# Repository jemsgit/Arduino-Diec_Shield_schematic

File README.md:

Arduino-Diec_Shield_schematic
=======

Schematics and boards

Arduino Diecimila - shc and brd for Arduino Atmega 168p
Arduino Shield - shield for servo, sound, led and power supply

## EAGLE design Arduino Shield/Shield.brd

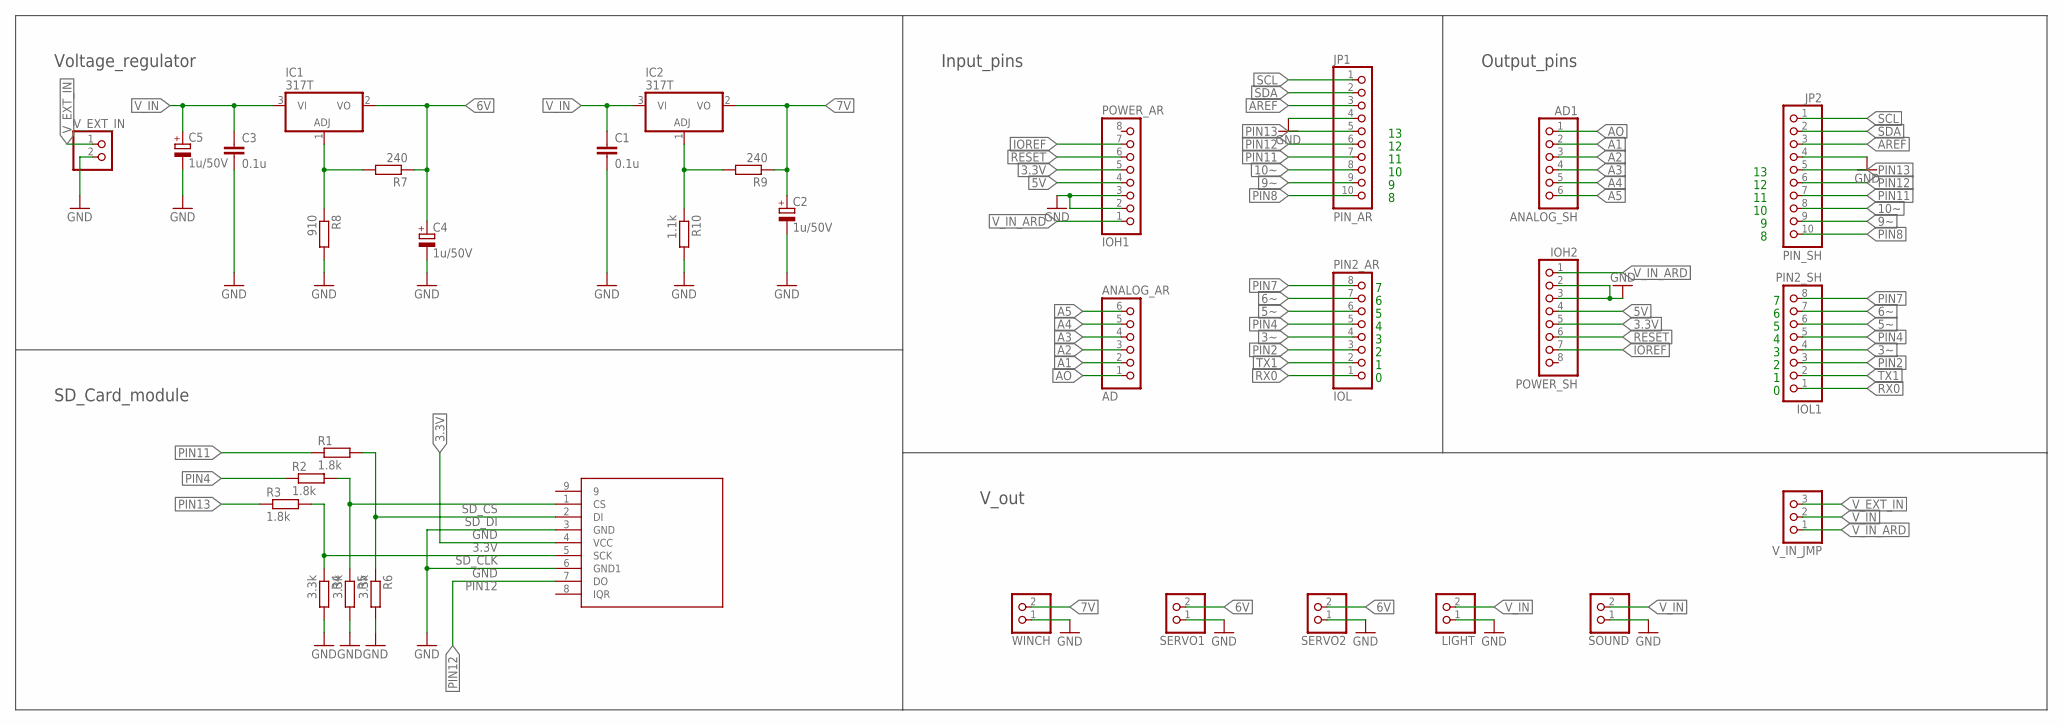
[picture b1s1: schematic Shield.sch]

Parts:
AD: ANALOG_AR; 1X06@1
AD1: ANALOG_SH; 1X06@1
C1, C3: 0.1u; C0805
C2, C4, C5: 1u/50V; E3,5-8
IC1, IC2: 317T; TO220H
IOH1: POWER_AR; 1X08
IOH2: POWER_SH; 1X08
IOL: PIN2_AR; 1X08@1
IOL1: PIN2_SH; 1X08@1
JP1: PIN_AR; 1X10
JP2: PIN_SH; 1X10
LIGHT: PINHD-1X2; 1X02
R1, R2, R3: 1.8k; R0805
R4, R5, R6: 3.3k; R0805
R7, R9: 240; R0805
R8: 910; R0805
R10: 1.1k; R0805
SERVO1, SERVO2: PINHD-1X2; 1X02
SOUND: PINHD-1X2; 1X02
U$1: SDCARDVAR2; SDCMF-10915W010
V_EXT_IN: PINHD-1X2; 1X02
V_IN_JMP: PINHD-1X3; 1X03
WINCH: PINHD-1X2; 1X02

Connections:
3.3V: IOH1.5, IOH2.5, U$1.4 (VCC)
3~: IOL.4, IOL1.4
5V: IOH1.4, IOH2.4
5~: IOL.6, IOL1.6
6V: C4.+, IC1.2 (VO), R7.1, SERVO1.2, SERVO2.2
6~: IOL.7, IOL1.7
7V: C2.+, IC2.2 (VO), R9.1, WINCH.2
9~: JP1.9, JP2.9
10~: JP1.8, JP2.8
A1: AD.2, AD1.2
A2: AD.3, AD1.3
A3: AD.4, AD1.4
A4: AD.5, AD1.5
A5: AD.6, AD1.6
AO: AD.1, AD1.1
AREF: JP1.3, JP2.3
GND: C1.2, C2.-, C3.2, C4.-, C5.-, IOH1.2, IOH1.3, IOH2.2, IOH2.3, JP1.4, JP2.4, LIGHT.1, R4.2, R5.2, R6.2, R8.2, R10.2, SERVO1.1, SERVO2.1, SOUND.1, U$1.3 (GND), U$1.6 (GND1), V_EXT_IN.2, WINCH.1
IOREF: IOH1.7, IOH2.7
unnamed: IC1.1 (ADJ), R7.2, R8.1
unnamed: IC2.1 (ADJ), R9.2, R10.1
PIN2: IOL.3, IOL1.3
PIN4: IOL.5, IOL1.5, R2.1
PIN7: IOL.8, IOL1.8
PIN8: JP1.10, JP2.10
PIN11: JP1.7, JP2.7, R1.1
PIN12: JP1.6, JP2.6, U$1.7 (DO)
PIN13: JP1.5, JP2.5, R3.1
RESET: IOH1.6, IOH2.6
RX0: IOL.1, IOL1.1
SCL: JP1.1, JP2.1
SDA: JP1.2, JP2.2
SD_CLK: R3.2, R4.1, U$1.5 (SCK)
SD_CS: R2.2, R5.1, U$1.1 (CS)
SD_DI: R1.2, R6.1, U$1.2 (DI)
TX1: IOL.2, IOL1.2
V_EXT_IN: V_EXT_IN.1, V_IN_JMP.3
V_IN: C1.1, C3.1, C5.+, IC1.3 (VI), IC2.3 (VI), LIGHT.2, SOUND.2, V_IN_JMP.2
V_IN_ARD: IOH1.1, IOH2.1, V_IN_JMP.1

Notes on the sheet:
Voltage_regulator
SD_Card_module
Input_pins
Output_pins
V_out

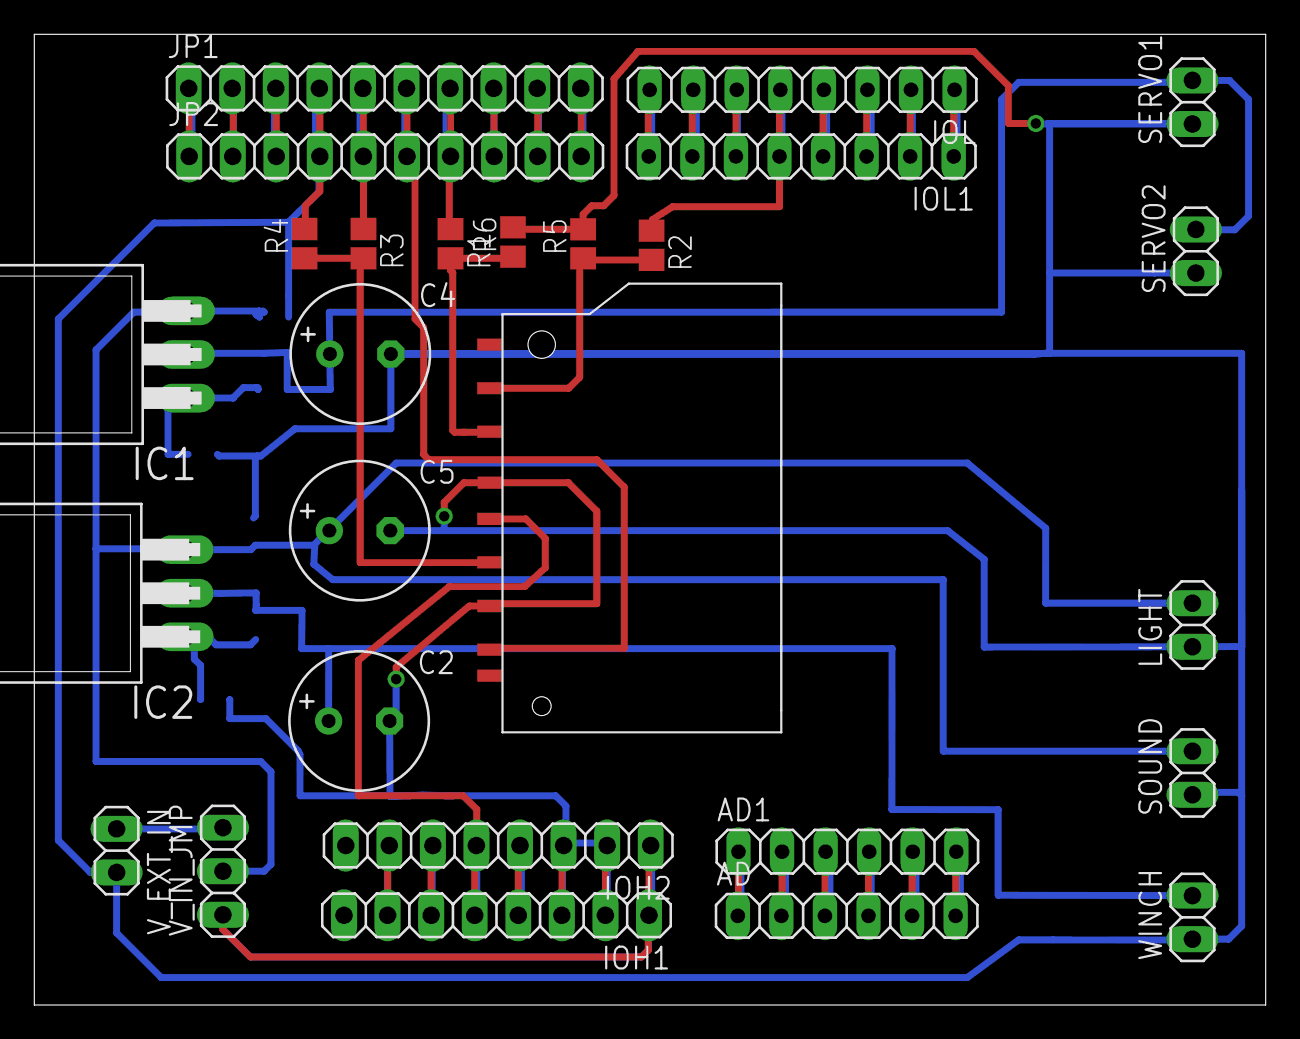
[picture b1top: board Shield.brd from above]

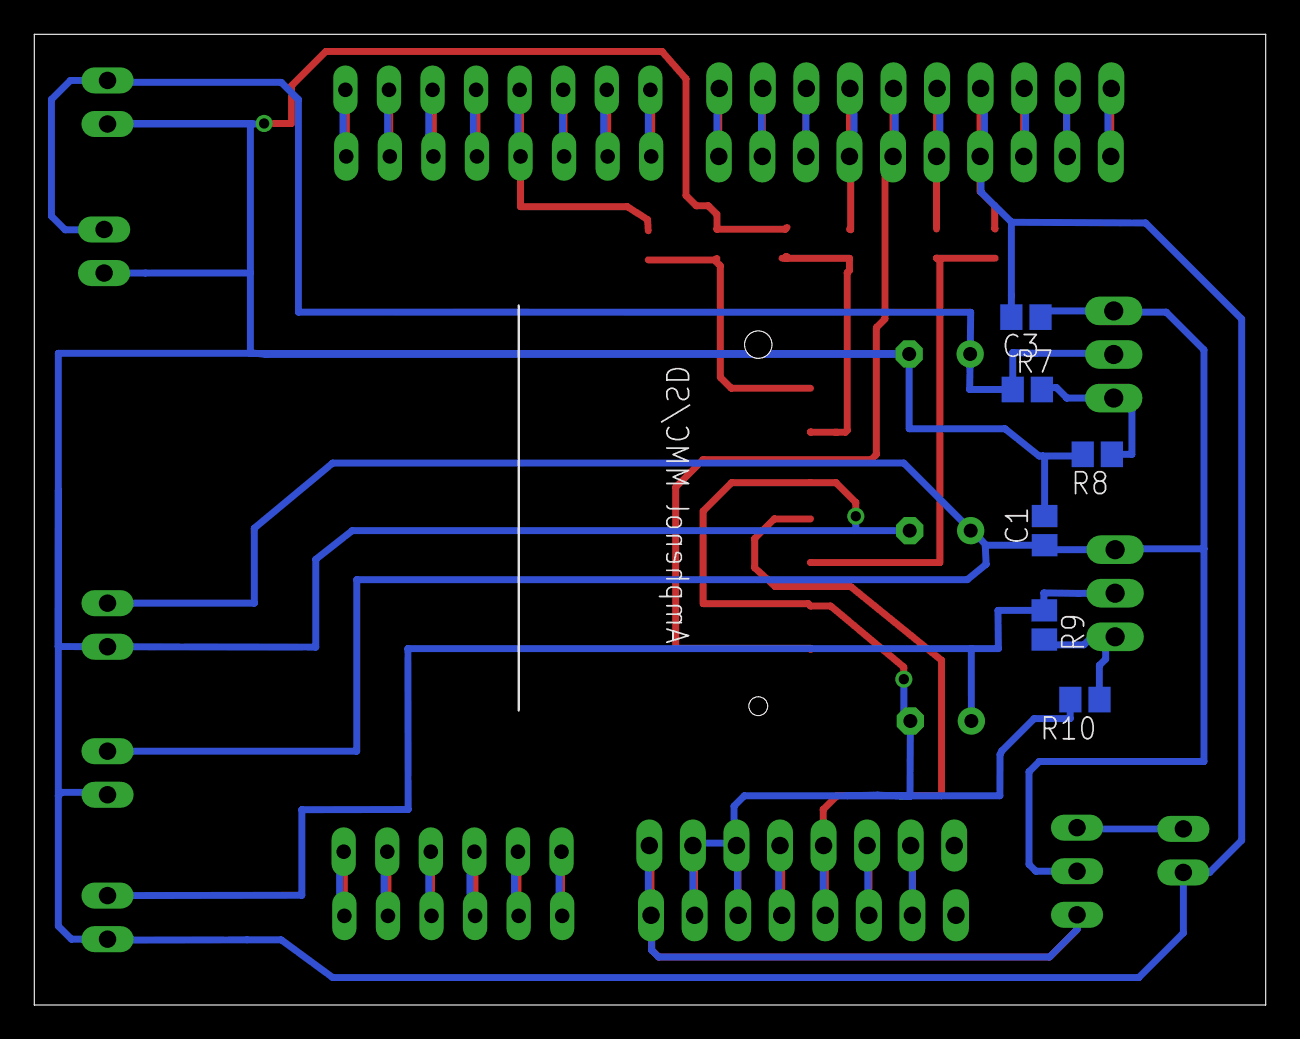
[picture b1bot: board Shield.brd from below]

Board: 2 copper layers, 71.7 x 56.5 mm, 33 parts (6 on the bottom side), 38 nets.

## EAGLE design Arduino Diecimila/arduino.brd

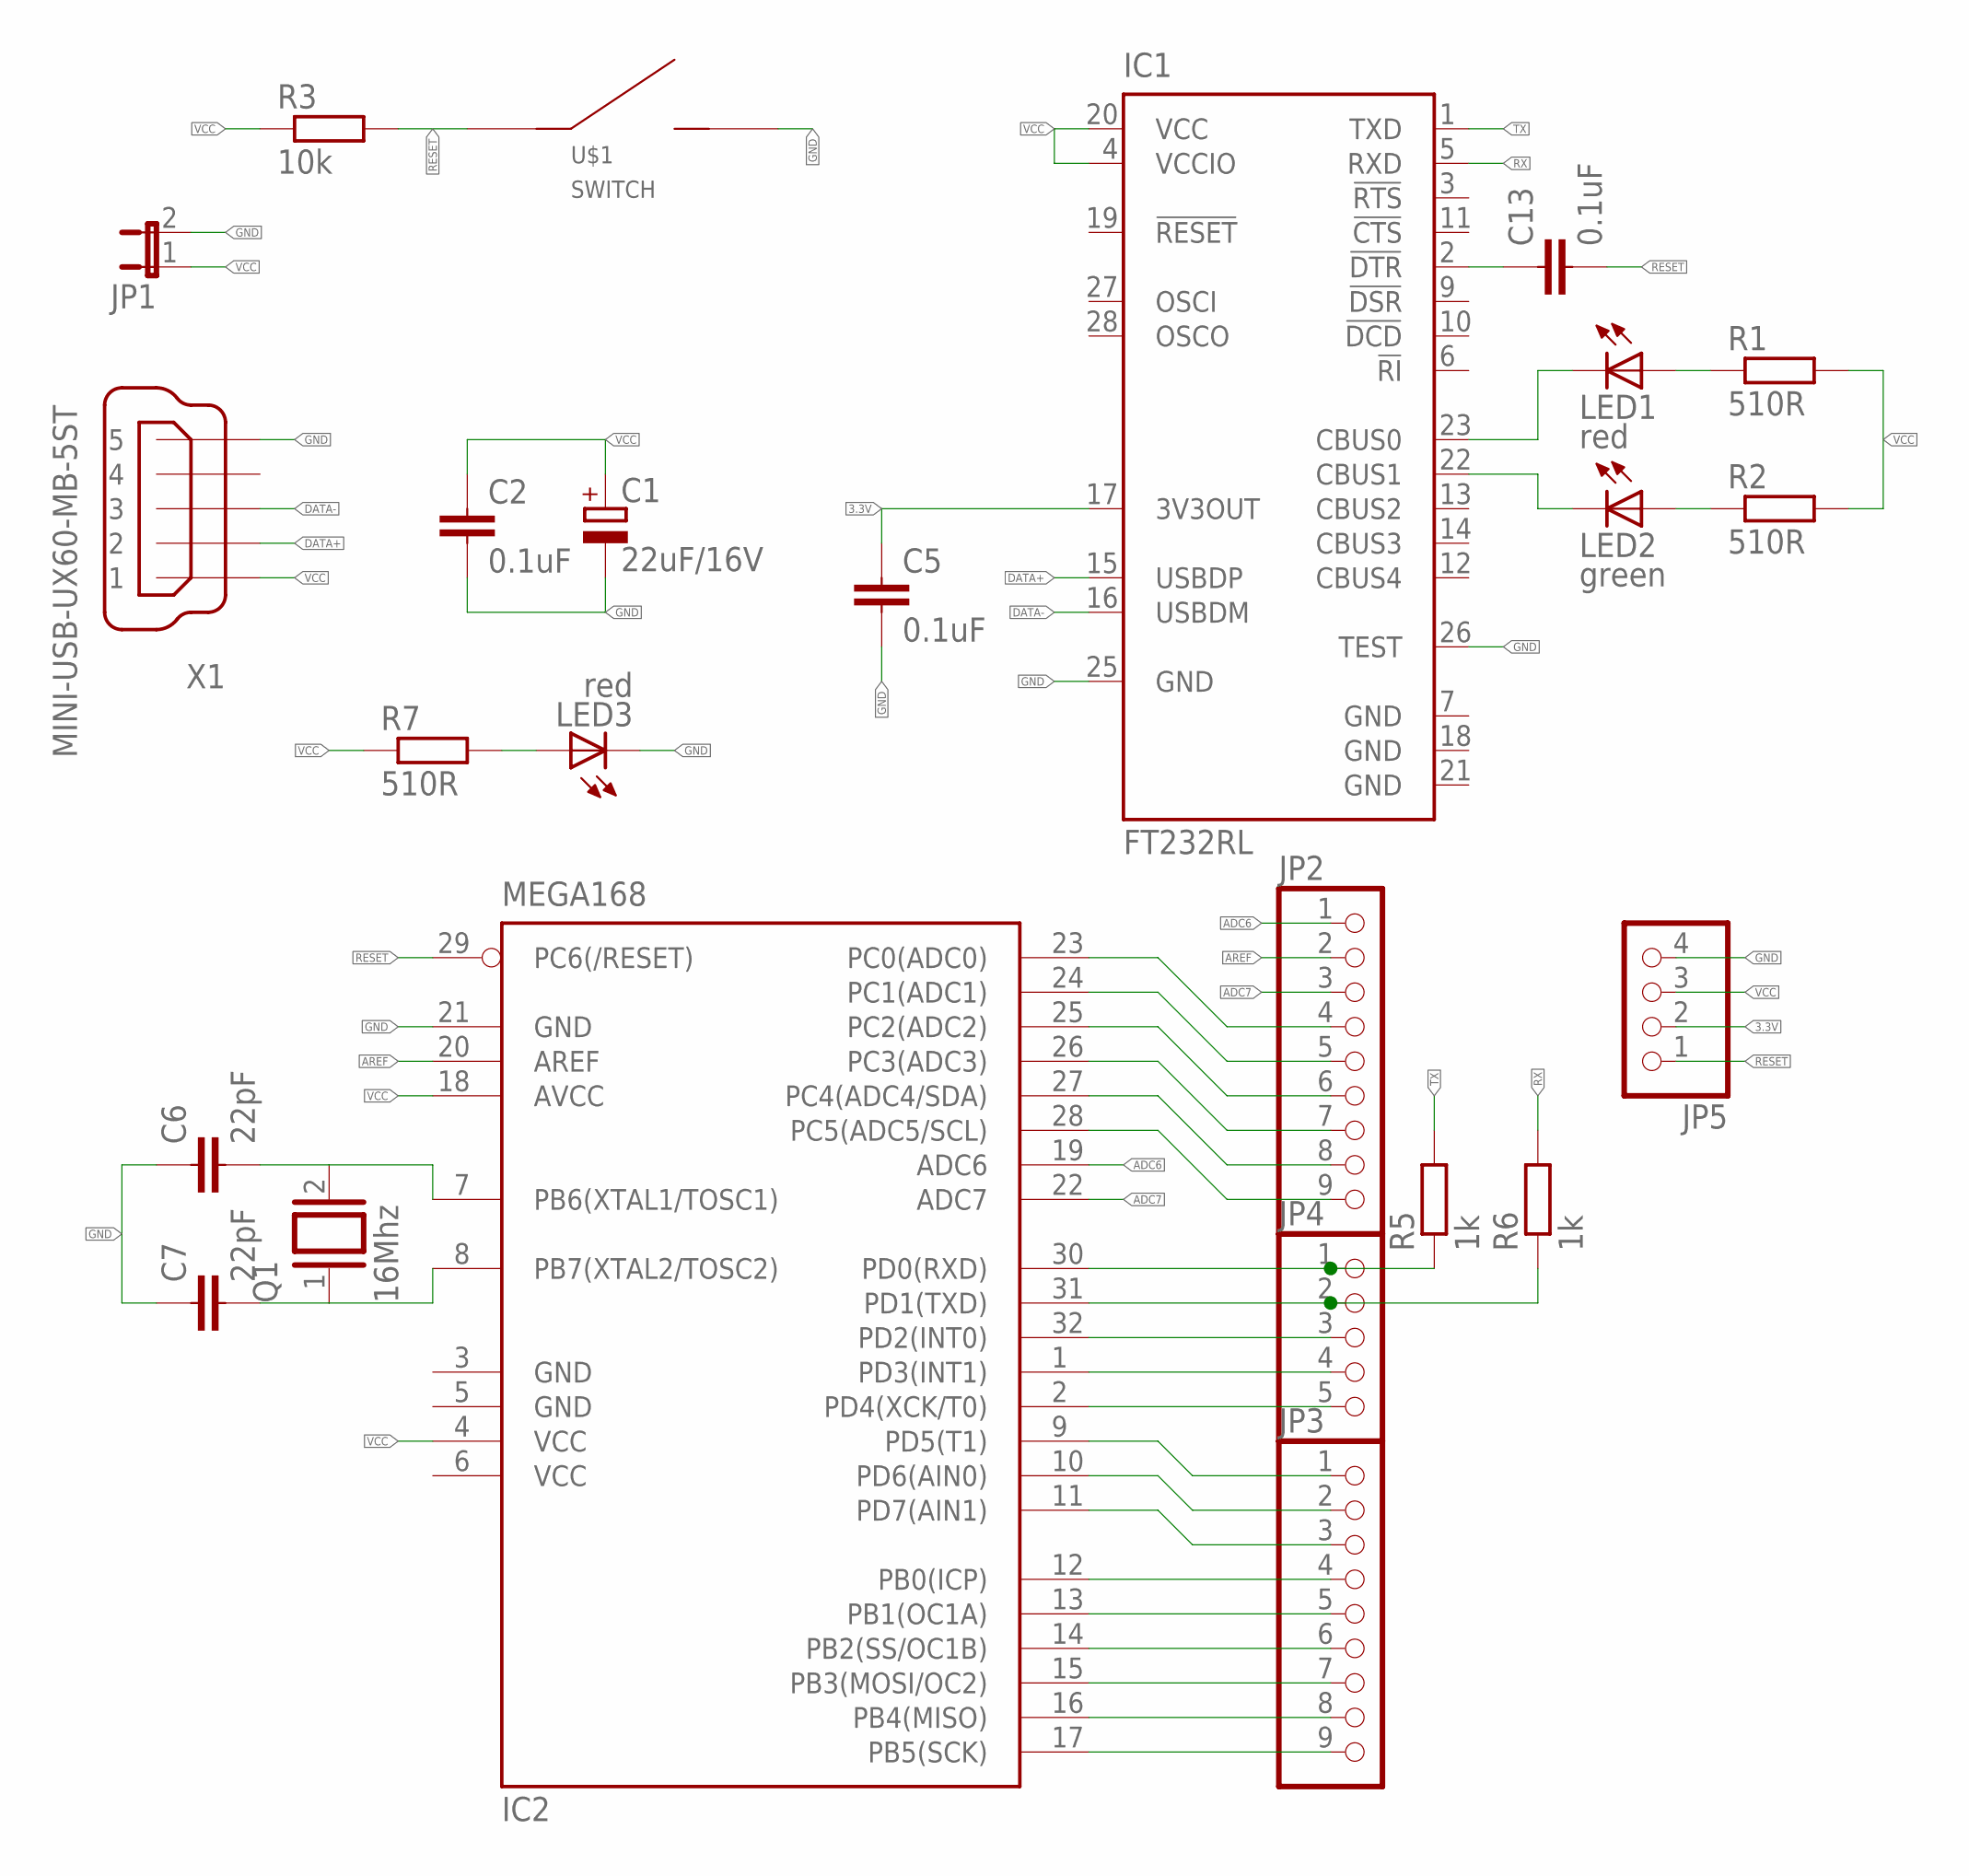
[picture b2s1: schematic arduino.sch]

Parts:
C1: 22uF/16V; E2-5
C2, C5, C13: 0.1uF; C0805K
C6, C7: 22pF; C0805K
IC1: FT232RL; SSOP28
IC2: MEGA168; TQFP32-08
JP1: JP1E; JP1
JP2, JP3: PINHD-1X9; 1X09
JP4: PINHD-1X5; 1X05
JP5: PINHD-1X4; 1X04
LED1, LED3: red; CHIPLED_1206
LED2: green; CHIPLED_1206
Q1: 16Mhz; QS
R1, R2, R7: 510R; R0805W
R3: 10k; R0805W
R5, R6: 1k; R0805W
U$1: SWITCH
X1: MINI-USB-UX60-MB-5ST; UX60-MB-5ST

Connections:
3.3V: C5.1, IC1.17 (3V3OUT), JP5.2
ADC6: IC2.19 (ADC6), JP2.1
ADC7: IC2.22 (ADC7), JP2.3
AREF: IC2.20 (AREF), JP2.2
DATA+: IC1.15 (USBDP), X1.2
DATA-: IC1.16 (USBDM), X1.3
GND: C1.-, C2.2, C5.2, C6.1, C7.1, IC1.7 (GND), IC1.18 (GND), IC1.21 (GND), IC1.25 (GND), IC1.26 (TEST), IC2.3 (GND), IC2.5 (GND), IC2.21 (GND), JP1.2, JP5.4, LED3.C, U$1.P2, X1.5
unnamed: IC1.22 (CBUS1), LED2.C
unnamed: IC1.23 (CBUS0), LED1.C
unnamed: LED1.A, R1.1
unnamed: LED2.A, R2.1
unnamed: C13.1, IC1.2 (!DTR)
unnamed: C6.2, IC2.7 (PB6(XTAL1/TOSC1)), Q1.2
unnamed: C7.2, IC2.8 (PB7(XTAL2/TOSC2)), Q1.1
unnamed: IC2.23 (PC0(ADC0)), JP2.4
unnamed: IC2.30 (PD0(RXD)), JP4.1, R5.1
unnamed: IC2.31 (PD1(TXD)), JP4.2, R6.1
unnamed: LED3.A, R7.2
unnamed: IC2.24 (PC1(ADC1)), JP2.5
unnamed: IC2.25 (PC2(ADC2)), JP2.6
unnamed: IC2.26 (PC3(ADC3)), JP2.7
unnamed: IC2.27 (PC4(ADC4/SDA)), JP2.8
unnamed: IC2.28 (PC5(ADC5/SCL)), JP2.9
unnamed: IC2.11 (PD7(AIN1)), JP3.3
unnamed: IC2.10 (PD6(AIN0)), JP3.2
unnamed: IC2.12 (PB0(ICP)), JP3.4
unnamed: IC2.13 (PB1(OC1A)), JP3.5
unnamed: IC2.14 (PB2(SS/OC1B)), JP3.6
unnamed: IC2.15 (PB3(MOSI/OC2)), JP3.7
unnamed: IC2.16 (PB4(MISO)), JP3.8
unnamed: IC2.17 (PB5(SCK)), JP3.9
unnamed: IC2.9 (PD5(T1)), JP3.1
unnamed: IC2.32 (PD2(INT0)), JP4.3
unnamed: IC2.1 (PD3(INT1)), JP4.4
unnamed: IC2.2 (PD4(XCK/T0)), JP4.5
RESET: C13.2, IC2.29 (PC6(/RESET)), JP5.1, R3.2, U$1.P1
RX: IC1.5 (RXD), R6.2
TX: IC1.1 (TXD), R5.2
VCC: C1.+, C2.1, IC1.4 (VCCIO), IC1.20 (VCC), IC2.4 (VCC), IC2.6 (VCC), IC2.18 (AVCC), JP1.1, JP5.3, R1.2, R2.2, R3.1, R7.1, X1.1

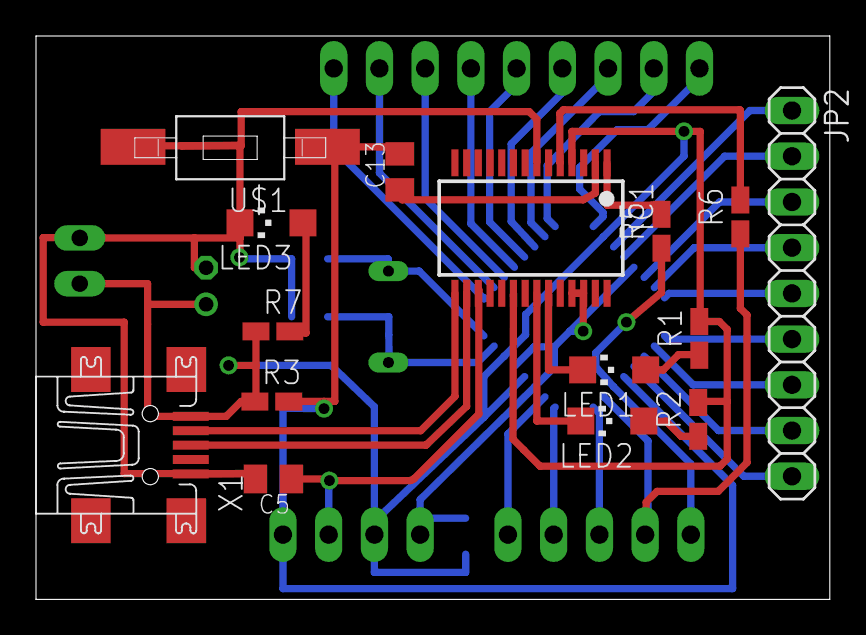
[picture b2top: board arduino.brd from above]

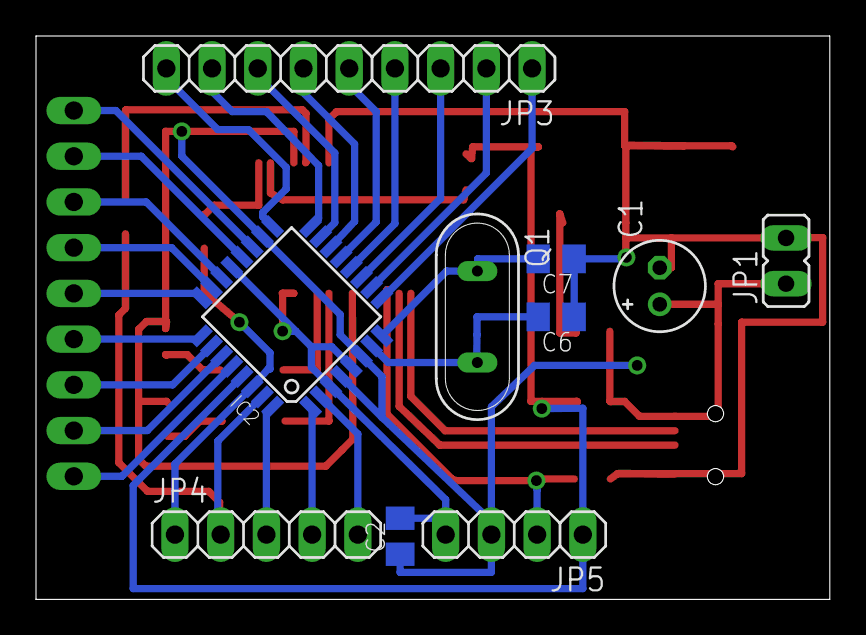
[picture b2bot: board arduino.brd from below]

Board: 2 copper layers, 44.1 x 31.3 mm, 25 parts (10 on the bottom side), 39 nets.

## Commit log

2013-10-07 Schem of shield
2013-10-08 Разводка платы
2013-10-08 Конечная разводка
2013-10-08 Больше места под sd
